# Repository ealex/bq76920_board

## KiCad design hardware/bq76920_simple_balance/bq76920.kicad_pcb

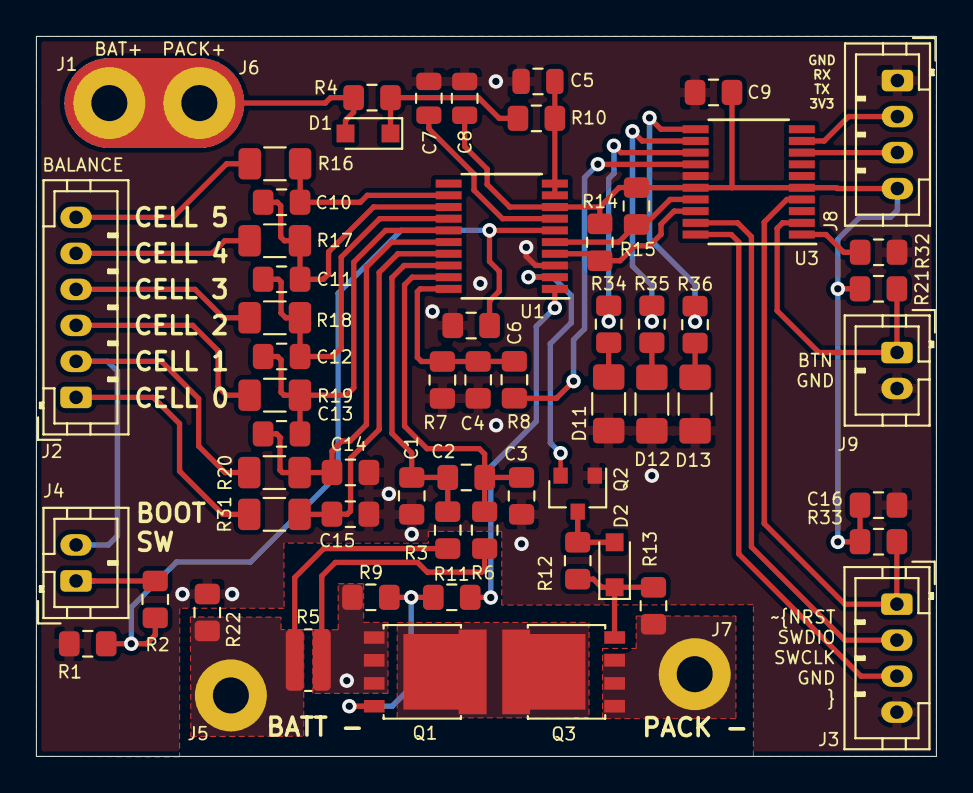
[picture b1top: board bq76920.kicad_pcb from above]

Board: 2 copper layers, 50.0 x 40.0 mm, 63 parts (0 on the bottom side), 48 nets.

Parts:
C1, C2, C3: 100n; C_0805_2012Metric_Pad1.15x1.40mm_HandSolder
C4, C6: 1n; C_0805_2012Metric_Pad1.15x1.40mm_HandSolder
C5, C7, C8: CGA4J1X7R1V475K125AC; C_0805_2012Metric
C9, C16: 100nF; C_0805_2012Metric_Pad1.15x1.40mm_HandSolder
C10, C11, C12, C13, C14, C15: 1u; C_0805_2012Metric_Pad1.15x1.40mm_HandSolder
D1, D2: PMEG3010BEA,115; D_SOD-323_HandSoldering
D11, D12, D13: APTD3216SURCK; C_1206_3216Metric_Pad1.42x1.75mm_HandSolder
J1: BAT+; power_pin
J2: Conn_01x06; JST_PH_B6B-PH-K_1x06_P2.00mm_Vertical
J3, J8: Conn_01x04; JST_PH_B4B-PH-K_1x04_P2.00mm_Vertical
J4: boot_switch; JST_PH_B2B-PH-K_1x02_P2.00mm_Vertical
J5: BAT-; power_pin
J6: PACK+; power_pin
J7: PACK-; power_pin
J9: RESET; JST_PH_B2B-PH-K_1x02_P2.00mm_Vertical
Q1, Q3: PSMN2R6-40YS; LFPAK56
Q2: SI2337DS-T1-E3; SOT-23
R1, R2, R4, R11, R14, R15, R21, R32, R33, R34, R35, R36: 10k; R_0805_2012Metric_Pad1.15x1.40mm_HandSolder
R3, R6, R8, R10: 100; R_0805_2012Metric_Pad1.15x1.40mm_HandSolder
R5: LTR18EZPFU10L0; R_0612_1632Metric
R7: 500k; R_0805_2012Metric_Pad1.15x1.40mm_HandSolder
R9, R12, R13: 1Meg; R_0805_2012Metric_Pad1.15x1.40mm_HandSolder
R16, R17, R18, R19, R20, R31: 100; R_1206_3216Metric
R22: 0; R_0805_2012Metric_Pad1.15x1.40mm_HandSolder
U1: bq7692006PW; TSSOP-20_4.4x6.5mm_P0.65mm
U3: STM32L031F4Px; TSSOP-20_4.4x6.5mm_P0.65mm

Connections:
+3V3: C8.2, C9.1, C16.1, J8.4, R14.2, R15.2, R21.1, R33.1, U1.8, U3.5, U3.16
/BAT+: D1.2, J1.1, J6.1, R4.2
/BAT-: J5.1, R3.2, R5.2, R22.1
/BAT_THERM: C6.2, R1.1, R2.1, U1.6
/RAW_BATT-: J2.1, R31.2
/RAW_C1: J2.2, J4.2, R20.2
/RAW_C2: J2.3, R19.2
/RAW_C3: J2.4, R18.2
/RAW_C4: J2.5, R17.2
/RAW_C5: J2.6, R16.2
/balance section/BAL_C0: C15.1, R31.1, U1.17
/balance section/BAL_C1: C13.2, C14.1, R20.1, U1.16
/balance section/BAL_C2: C12.2, C13.1, R19.1, U1.15
/balance section/BAL_C3: C11.2, C12.1, R18.1, U1.14
/balance section/BAL_C4: C10.2, C11.1, R17.1, U1.13
/balance section/BAL_C5: C10.1, R16.1, U1.12
/bq76920 section/PACK-: J7.1, Q3.1, Q3.2, Q3.3, R13.2
/cpu/BTN: J9.1, R21.2, U3.2
/cpu/PACK_ALERT: R8.1, U3.14
/cpu/PACK_SCL: R15.1, U1.5, U3.17
/cpu/PACK_SDA: R14.1, U1.4, U3.18
/cpu/SWCLK: J3.3, U3.20
/cpu/SWDIO: J3.2, U3.19
/cpu/USART2_RX: J8.2, U3.9
/cpu/USART2_TX: J8.3, U3.8
/cpu/~NRST: J3.1, R33.2, U3.4
GND: C1.2, C3.1, C4.1, C5.1, C6.1, C7.1, C8.1, C9.2, C14.2, C15.2, C16.2, D11.1, D12.1, D13.1, J3.4, J8.1, J9.2, Q2.1, R1.2, R7.2, R22.2, R32.2, U1.3, U3.15
unnamed: C1.1, C2.2, R3.1, U1.18
unnamed: C2.1, C3.2, R6.1, U1.19
unnamed: C4.2, R7.1, R8.2, U1.20
unnamed: C5.2, R10.1, U1.9, U1.10
unnamed: C7.2, U1.7
unnamed: D1.1, R4.1, R10.2
unnamed: D2.1, Q3.4, R12.2, R13.1
unnamed: D2.2, Q2.3, R12.1
unnamed: D11.2, R34.2
unnamed: D12.2, R35.2
unnamed: D13.2, R36.2
unnamed: J4.1, R2.2
unnamed: Q1.1, Q1.2, Q1.3, R5.1, R6.2, R9.2
unnamed: Q1.4, R9.1, R11.2
unnamed: Q1.5, Q3.5
unnamed: Q2.2, U1.2
unnamed: R11.1, U1.1
unnamed: R32.1, U3.1
unnamed: R34.1, U3.13
unnamed: R35.1, U3.12
unnamed: R36.1, U3.11

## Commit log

2020-01-06 add all files over here, from the locally developed project
2020-01-06 remove old project data
2020-01-06 update cpu and reduce BOM
2020-01-06 update bom
2020-01-07 update BOM, arrange some files
2020-01-07 clean up, adnotate, footprints
2020-01-08 final pcb version
2020-01-08 create manufacture data, start prototype production
2020-02-29 add STM32 cube based version
2020-03-02 add communication and balancing algorithms
2020-07-30 update fw
2020-10-04 update gitignore
2020-10-04 update firmware
2021-11-18 code update
2021-12-02 simple balance board, 1 sided version
